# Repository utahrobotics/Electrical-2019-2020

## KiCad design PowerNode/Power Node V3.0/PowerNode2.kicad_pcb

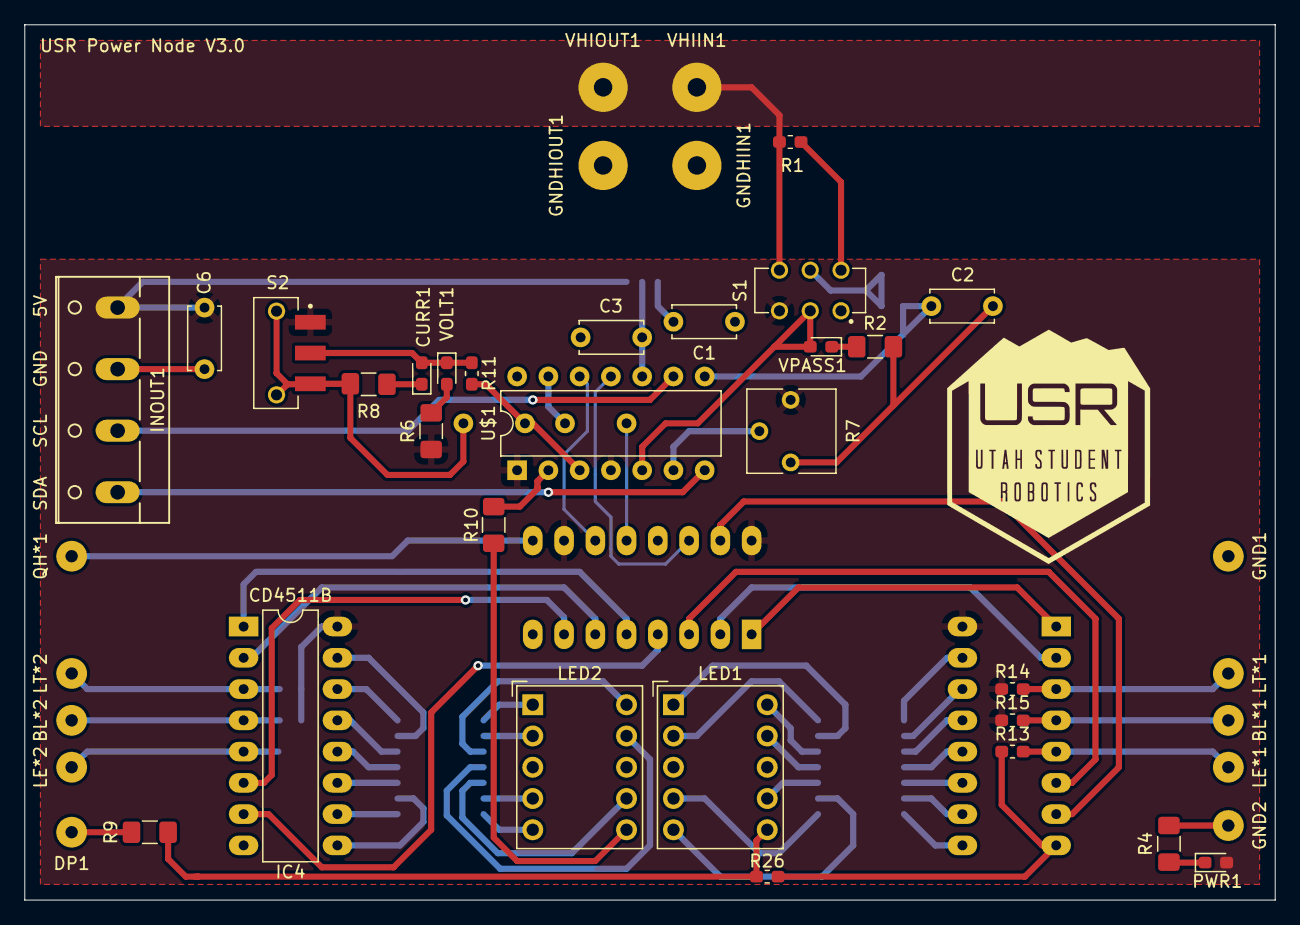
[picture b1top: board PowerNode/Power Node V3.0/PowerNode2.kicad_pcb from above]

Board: 2 copper layers, 101.6 x 71.1 mm, 55 parts (0 on the bottom side), 70 nets.

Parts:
BL*1, BL*2: 2,54_0,9; SolderWirePad_1x01_Drill1mm
C1: 1nF; C_Disc_D5.0mm_W2.5mm_P5.00mm
C2, C3, C4, C5, C6: 0.1uF; C_Disc_D5.0mm_W2.5mm_P5.00mm
CURR1: LED; LED_0603_1608Metric_Pad1.05x0.95mm_HandSolder
DP1: 2,54_0,9; SolderWirePad_1x01_Drill1mm
GND1, GND2: 2,15_1,0; SolderWirePad_1x01_Drill1mm
GNDHIIN1: WIREPAD4,16O1,6; SolderWirePad_1x01_Drill1.5mm
GNDHIOUT1: WIREPAD4,16O1,6; SolderWirePad_1x01_Drill1.5mm
IC1: ACS712xLCTR-30A; SOIC-8_3.9x4.9mm_P1.27mm
IC2: 74HC594N; DIP-16_W7.62mm_LongPads
IC3, IC4: CD4511B; DIP-16_W7.62mm_LongPads
INOUT1: W237-4
LE*1, LE*2: 2,54_0,9; SolderWirePad_1x01_Drill1mm
LED1, LED2: LTS-4301P; Sx39-1xxxxx
LT*1, LT*2: 2,54_0,9; SolderWirePad_1x01_Drill1mm
PWR1: LED; LED_0603_1608Metric_Pad1.05x0.95mm_HandSolder
QH*1: 2,54_0,9; SolderWirePad_1x01_Drill1mm
R1: 43k; R_0603_1608Metric_Pad1.05x0.95mm_HandSolder
R2, R4, R6, R8, R9, R10: 220; R_1206_3216Metric_Pad1.42x1.75mm_HandSolder
R3, R5, R11, R12, R13, R14, R15, R16, R17, R18, R26: 10k; R_0603_1608Metric_Pad1.05x0.95mm_HandSolder
R7: 100k; Potentiometer_Vishay_T73YP_Vertical
RN1, RN2: 220; SOIC127P762X240-14N
S1: JS202011CQN
S2: JS102011SAQN
U$1: ATtiny84-20PU; DIP-14_W7.62mm
VHIIN1: WIREPAD4,16O1,6; SolderWirePad_1x01_Drill1.5mm
VHIOUT1: WIREPAD4,16O1,6; SolderWirePad_1x01_Drill1.5mm
VOLT1: LED; LED_0603_1608Metric_Pad1.05x0.95mm_HandSolder
VPASS1: LED; LED_0603_1608Metric_Pad1.05x0.95mm_HandSolder

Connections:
/DP1: LED1.6, R9.2, R26.2
/DP2: LED2.6, R10.1
/GNDHIOUT: GNDHIOUT1.1, IC1.1, IC1.2
/IMEAS: C3.1, IC1.7, U$1.10
/SCL: INOUT1.2, U$1.9
/SDA: INOUT1.1, U$1.7
/SWITCH: CURR1.2, R11.2, S2.2, VOLT1.1
/VHI: R1.2, S1.6, VHIIN1.1, VHIOUT1.1
/VMEAS: R3.1, R5.1, S1.5
/VMEAS_1: C2.1, R5.2, U$1.8
/VPASS: S1.2, U$1.5, VPASS1.2
/VPOT: R7.2, U$1.6
/a1: LED1.10, RN1.5
/a2: LED2.10, RN2.10
/b1: LED1.9, RN1.4
/b2: LED2.9, RN2.11
/c1: LED1.7, RN1.3
/c2: LED2.7, RN2.12
/d1: LED1.5, RN1.2
/d2: LED2.5, RN2.14
/e1: LED1.4, RN1.1
/e2: LED2.4, RN2.13
/f1: LED1.2, RN1.7
/f2: LED2.2, RN2.9
/g1: LED1.1, RN1.6
/g2: LED2.1, RN2.8
/nBL1: BL*1.1, IC3.4, R15.2
/nBL2: BL*2.1, IC4.4, R18.2
/nLE1: IC3.5, LE*1.1, R13.2
/nLE2: IC4.5, LE*2.1, R16.2
/nLT1: IC3.3, LT*1.1, R14.2
/nLT2: IC4.3, LT*2.1, R17.2
/nQH: IC2.9, QH*1.1, R12.2
GND: C1.2, C2.2, C3.2, C5.2, C6.2, GND1.1, GND2.1, GNDHIIN1.1, IC1.3, IC1.4, IC1.5, IC2.8, IC2.13, IC3.8, IC4.8, INOUT1.3, LED1.3, LED1.8, LED2.3, LED2.8, R2.1, R3.2, R4.1, R7.3, R8.1, R12.1, R13.1, R16.1, R26.1, S1.1, S2.3, U$1.14
unnamed: C1.1, IC1.6
unnamed: C4.1, IC2.12
unnamed: C4.2, U$1.13
unnamed: C5.1, R11.1, U$1.3
unnamed: CURR1.1, R8.2
unnamed: DP1.1, R9.1
unnamed: IC2.1, IC3.1
unnamed: IC2.2, IC3.2
unnamed: IC2.3, IC3.6
unnamed: IC2.4, IC4.7
unnamed: IC2.5, IC4.1
unnamed: IC2.6, IC4.2
unnamed: IC2.7, IC4.6
unnamed: IC2.11, U$1.12
unnamed: IC2.14, U$1.11
unnamed: IC2.15, IC3.7
unnamed: IC3.9, RN1.14
unnamed: IC3.10, RN1.13
unnamed: IC3.11, RN1.12
unnamed: IC3.12, RN1.11
unnamed: IC3.13, RN1.10
unnamed: IC3.14, RN1.9
unnamed: IC3.15, RN1.8
unnamed: IC4.9, RN2.2
unnamed: IC4.10, RN2.1
unnamed: IC4.11, RN2.3
unnamed: IC4.12, RN2.4
unnamed: IC4.13, RN2.5
unnamed: IC4.14, RN2.7
unnamed: IC4.15, RN2.6
unnamed: PWR1.1, R4.2
unnamed: R1.1, S1.4
unnamed: R2.2, VPASS1.1
unnamed: R6.1, VOLT1.2
unnamed: R10.2, U$1.2
Vdd: C6.1, IC1.8, IC2.10, IC2.16, IC3.16, IC4.16, INOUT1.4, PWR1.2, R6.2, R7.1, R14.1, R15.1, R17.1, R18.1, S1.3, S2.1, U$1.1, U$1.4

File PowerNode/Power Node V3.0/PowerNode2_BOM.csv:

Item,Qty,Total Qty,Reference(s),Value,Footprint,Datasheet,Description,Status,Notes
1,1,6,C1,1nF,Capacitor_THT:C_Disc_D5.0mm_W2.5mm_P5.00mm,~,Ceramic capacitor,Buy from stockroom,
2,5,30,"C2, C3, C4, C5, C6",0.1uF,Capacitor_THT:C_Disc_D5.0mm_W2.5mm_P5.00mm,~,Ceramic capacitor,Buy from stockroom,
3,1,6,IC1,ACS712xLCTR-30A,Package_SO:SOIC-8_3.9x4.9mm_P1.27mm,http://www.allegromicro.com/~/media/Files/Datasheets/ACS712-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,Current sense IC,Already in the lab,
4,1,6,IC2,74HC594N,Package_DIP:DIP-16_W7.62mm_LongPads,http://www.ti.com/lit/ds/symlink/sn74hc594.pdf,Serial to parallel converter,Buy from stockroom,
5,2,12,"IC3, IC4",CD4511B,Package_DIP:DIP-16_W7.62mm_LongPads,https://www.ti.com/lit/ds/symlink/cd4511b.pdf,LED driver,Buy from stockroom,
6,1,6,INOUT1,W237-4,PowerNode2:W237-4,~,Screw terminal,Buy online,
7,2,12,"LED1, LED2",LTS-4301P,Display_7Segment:Sx39-1xxxxx,https://www.datasheets360.com/pdf/-3279684472568245476,7 segment display,Buy from stockroom,Make sure they are common cathode
8,2,12,"PWR1, VPASS1",LED,LED_SMD:LED_0603_1608Metric_Pad1.05x0.95mm_HandSolder,~,SMD LED,Buy online,Check If<=20mA and Vf<=3.3V. Prefer amber/orange/red for VPASS1
9,1,6,R1,43k,Resistor_SMD:R_0603_1608Metric_Pad1.05x0.95mm_HandSolder,~,SMD resistor,Buy online,Check 0603 package
10,6,36,"R2, R4, R6, R8-10",220,Resistor_SMD:R_1206_3216Metric_Pad1.42x1.75mm_HandSolder,~,SMD resistor,Buy online,Check 1206 package
11,11,66,"R3, R5, R11-18, R26",10k,Resistor_SMD:R_0603_1608Metric_Pad1.05x0.95mm_HandSolder,~,SMD resistor,Buy online,Check 0603 package
12,1,6,R7,100k,Potentiometer_THT:Potentiometer_Vishay_T73YP_Vertical,~,100k potentiometer,Buy from stockroom?,Make sure it fits
13,2,12,"RN1, RN2",220,PowerNode2:SOIC127P762X240-14N,https://www.mouser.com/datasheet/2/54/4800P-777115.pdf,SMD resistor network,Buy online,Cheaper than separate resistors and makes soldering easier
14,1,6,S1,SW_DPDT,PowerNode2:OS202011MS2Qx1,https://www.mouser.com/datasheet/2/60/os-1382783.pdf,DPDT switch,Buy online,
15,1,6,S2,SW_SPDT,PowerNode2:OS102011MS2Qx1,https://www.mouser.com/datasheet/2/60/os-1382783.pdf,SPDT switch,Buy online,
16,1,6,U$1,ATtiny84-20PU,Package_DIP:DIP-14_W7.62mm,http://ww1.microchip.com/downloads/en/DeviceDoc/doc8006.pdf,ATTiny84 microcontroller,Already in lab?,
17,1,6,VOLT1,HSMF-C173,PowerNode2:HSMFC173,https://docs.broadcom.com/docs/HSMF-C173-DS,SMD Bi-color LED,Buy online,Prefer colors different from VPASS1 and PWR1. Other similar package OK but tell me

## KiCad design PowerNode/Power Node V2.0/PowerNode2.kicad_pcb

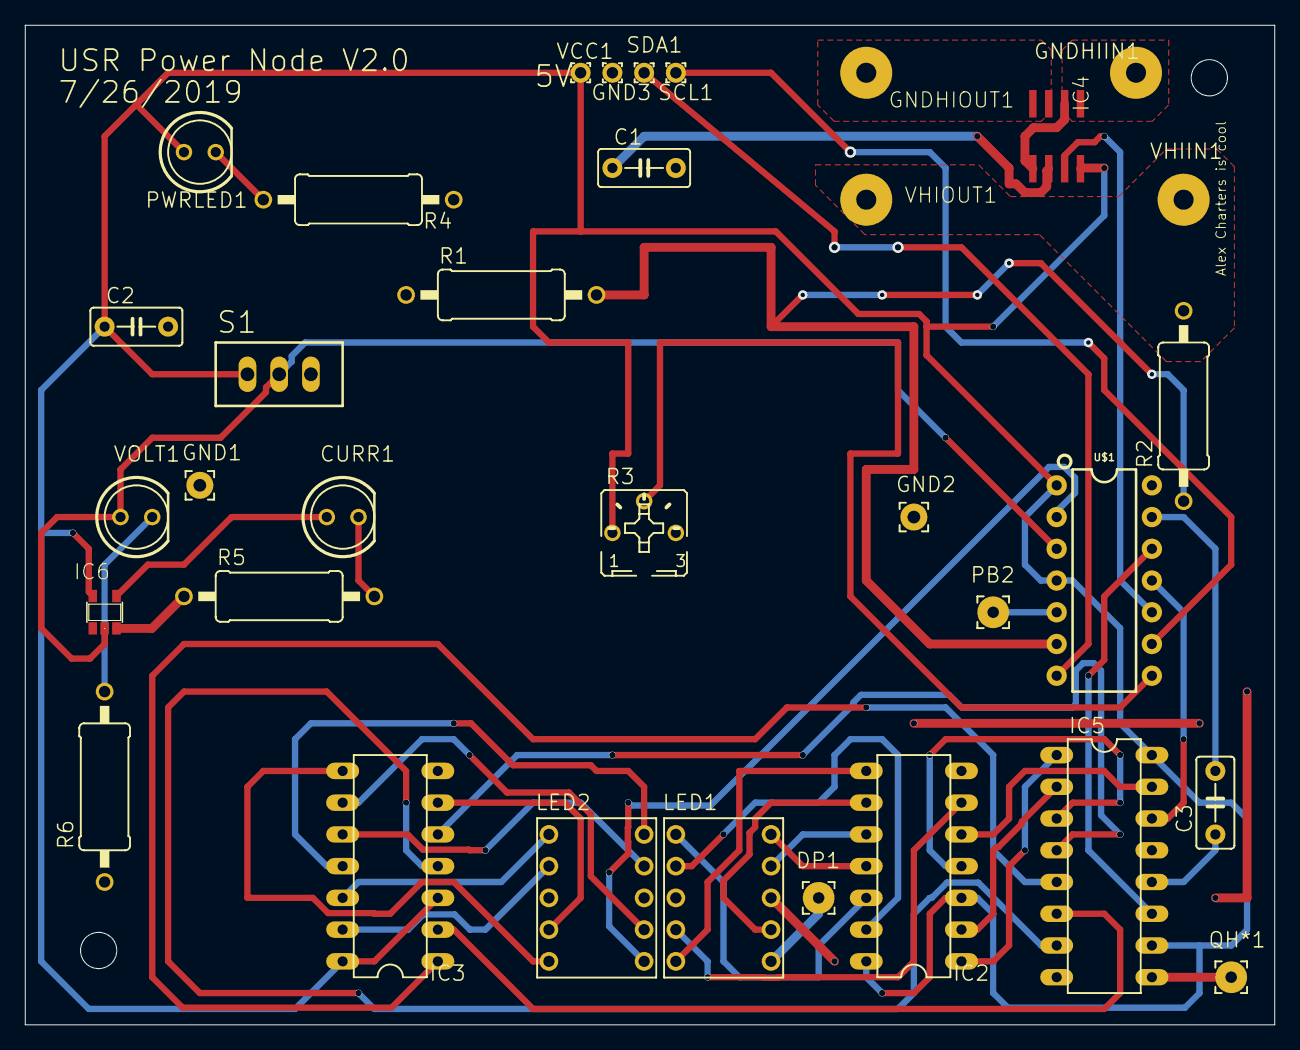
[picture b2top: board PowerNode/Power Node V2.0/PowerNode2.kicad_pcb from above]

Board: 2 copper layers, 100.0 x 80.0 mm, 36 parts (0 on the bottom side), 45 nets.

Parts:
@HOLE0, @HOLE1: (no value)
C1: 1nF; C5B3
C2, C3: 0.1uF; C5B3
CURR1: LED5MM
DP1: 2,54_0,9
GND1, GND2: 2,15_1,0
GND3: WIREPAD1,6_0,9; 1,6_0,9
GNDHIIN1: WIREPAD4,16O1,6; 4,16O1,6
GNDHIOUT1: WIREPAD4,16O1,6; 4,16O1,6
IC2, IC3: 7449N; DIL14
IC4: ACS712-LC; SOIC8
IC5: 74595N; DIL16
IC6: 741G04DBV; SOT23-5
LED1, LED2: S4301B
PB2: 2,54_0,9
PWRLED1: LED5MM
QH*1: 2,54_0,9
R1: 300k; 0411_15
R2: 1.2M; 0411_15
R3: TRIM_US-B25P; B25P
R4, R5, R6: 330; 0411_15
S1: TL32PO; TL3XPO
SCL1: WIREPAD1,6_0,9; 1,6_0,9
SDA1: WIREPAD1,6_0,9; 1,6_0,9
U$1: ATTINY84ATTINY84-20PU; DIP14
VCC1: WIREPAD1,6_0,9; 1,6_0,9
VHIIN1: WIREPAD4,16O1,6; 4,16O1,6
VHIOUT1: WIREPAD4,16O1,6; 4,16O1,6
VOLT1: LED5MM

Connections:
/VCC: C2.1, IC2.3, IC2.14, IC3.3, IC3.14, IC4.8, IC5.10, IC5.16, IC6.5, PWRLED1.A, R3.A, S1.1, U$1.1, U$1.4, VCC1.1
unnamed: C1.1, IC4.6
unnamed: C1.2, C2.2, GND1.1, GND2.1, GND3.1, GNDHIIN1.1, IC2.7, IC3.7, IC4.1, IC4.2, IC4.5, IC5.8, IC5.13, IC6.3, LED1.3, LED1.8, LED2.3, LED2.8, R1.1, R3.E, R4.1, R5.1, R6.1, S1.3, U$1.14
unnamed: C3.1, IC5.12
unnamed: C3.2, U$1.13
unnamed: CURR1.A, IC6.4
unnamed: CURR1.K, R5.2
unnamed: DP1.1, LED1.6
unnamed: GNDHIOUT1.1, IC4.3, IC4.4
unnamed: IC2.1, IC5.1
unnamed: IC2.2, IC5.2
unnamed: IC2.4, IC5.3
unnamed: IC2.5, IC5.15
unnamed: IC2.6, LED1.4
unnamed: IC2.8, LED1.5
unnamed: IC2.9, LED1.7
unnamed: IC2.10, LED1.9
unnamed: IC2.11, LED1.10
unnamed: IC2.12, LED1.1
unnamed: IC2.13, LED1.2
unnamed: IC3.1, IC5.5
unnamed: IC3.2, IC5.6
unnamed: IC3.4, IC5.7
unnamed: IC3.5, IC5.4
unnamed: IC3.6, LED2.4
unnamed: IC3.8, LED2.5
unnamed: IC3.9, LED2.7
unnamed: IC3.10, LED2.9
unnamed: IC3.11, LED2.10
unnamed: IC3.12, LED2.1
unnamed: IC3.13, LED2.2
unnamed: IC4.7, U$1.10
unnamed: IC5.9, QH*1.1
unnamed: IC5.11, U$1.12
unnamed: IC5.14, U$1.11
unnamed: IC6.2, S1.2, U$1.3, VOLT1.A
unnamed: LED2.6, U$1.2
unnamed: PB2.1, U$1.5
unnamed: PWRLED1.K, R4.2
unnamed: R1.2, R2.1, U$1.6
unnamed: R2.2, VHIIN1.1, VHIOUT1.1
unnamed: R3.S, U$1.8
unnamed: R6.2, VOLT1.K
unnamed: SCL1.1, U$1.9
unnamed: SDA1.1, U$1.7

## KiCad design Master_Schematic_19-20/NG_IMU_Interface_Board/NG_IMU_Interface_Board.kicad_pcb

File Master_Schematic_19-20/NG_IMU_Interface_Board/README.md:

# NG_IMU_Interface_Board
Hardware files for powering and interfacing with a Northrup Grumman IMU

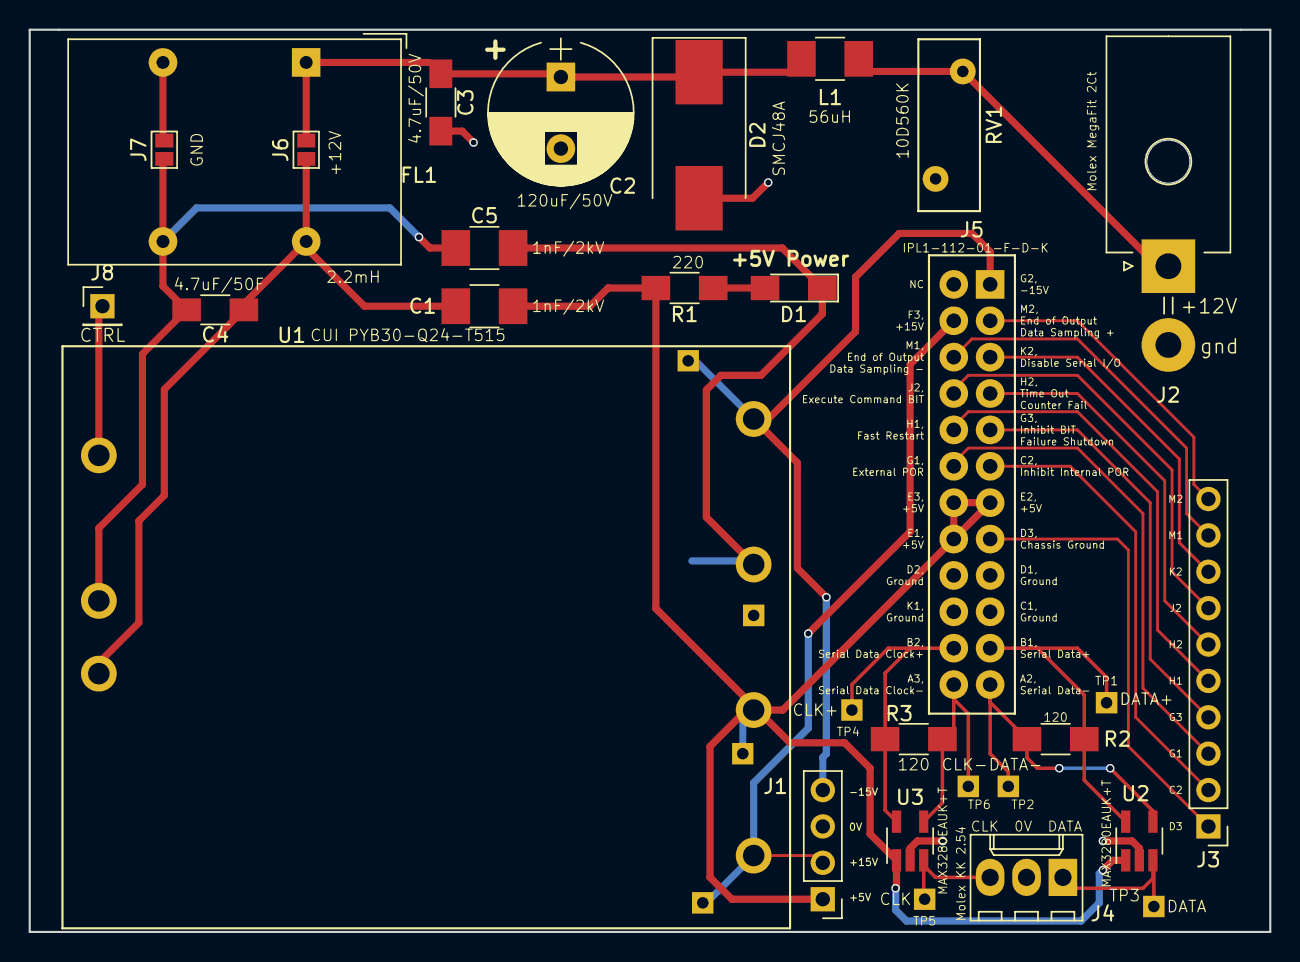
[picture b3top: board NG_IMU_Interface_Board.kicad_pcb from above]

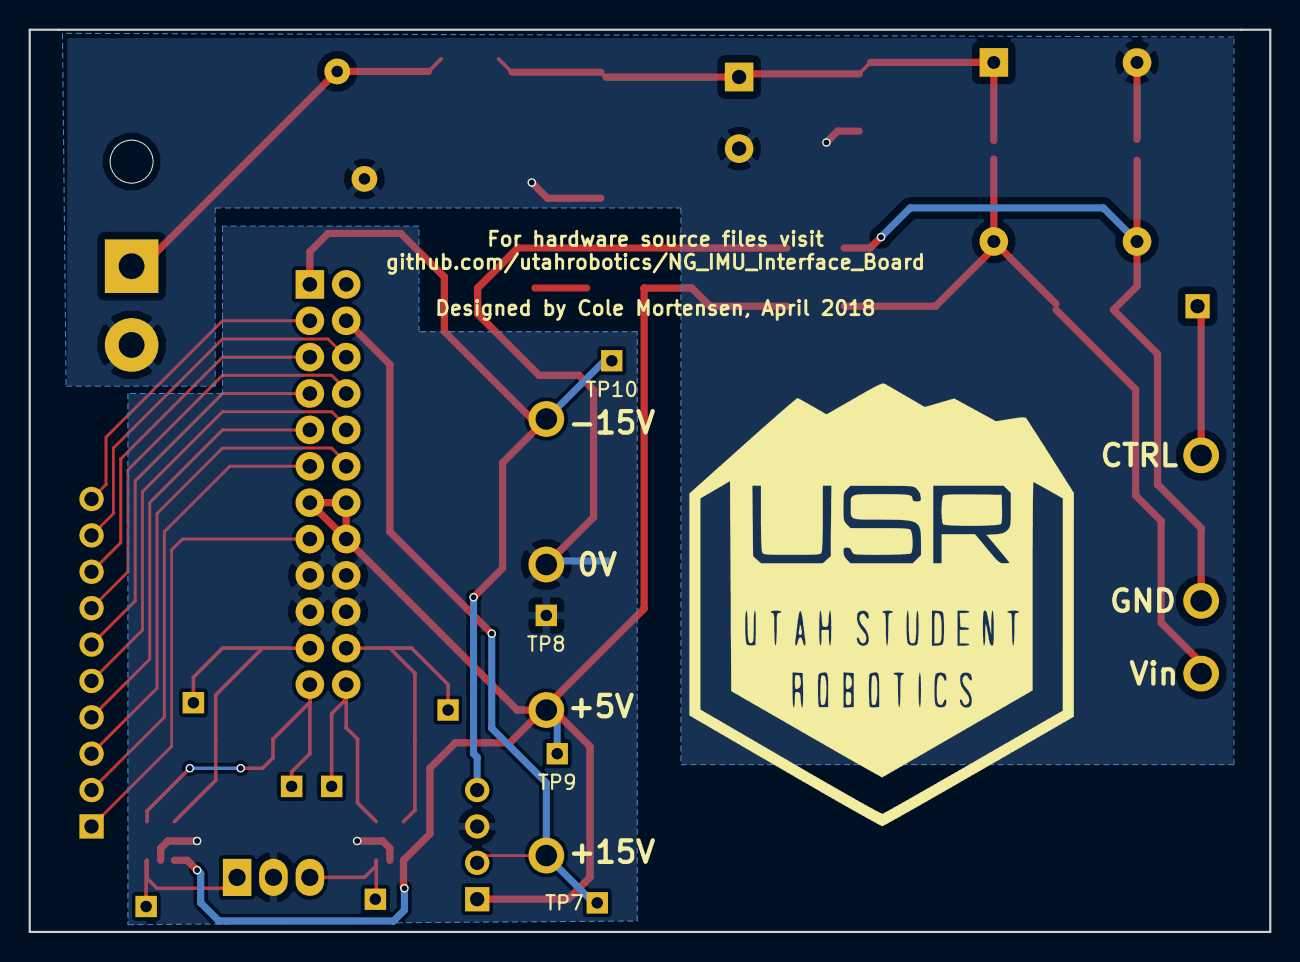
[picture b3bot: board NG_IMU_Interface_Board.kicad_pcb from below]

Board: 2 copper layers, 86.6 x 63.0 mm, 34 parts (4 on the bottom side), 27 nets.

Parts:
C1, C5: 1nF/2kV; C_1210_HandSoldering
C2: 120μF/50V; CP_Radial_D10.0mm_P5.00mm
C3, C4: 4.7μF/50V; C_1206_HandSoldering
D1: LED; LED_1206_HandSoldering
D2: SMCJ48A; D_SMC_Handsoldering
FL1: 2.2mH; Choke_Schaffner_RN214-04-15.5x23.0mm
J1: Conn_01x04; Pin_Header_Straight_1x04_Pitch2.54mm
J2: Conn_01x02; Molex_MegaFit_2x01x5.70mm_Angled
J3: Conn_01x10; Pin_Header_Straight_1x10_Pitch2.54mm
J4: Conn_01x03; Molex_KK-6410-03_03x2.54mm_Straight
J5: Conn_02x12_Top_Bottom; IPL1-112-01-F-D-K
J6, J7: GS2
J8: Conn_01x01; Pin_Header_Straight_1x01_Pitch2.54mm
L1: 56 uH; L_1210_HandSoldering
R1: 220; R_1206_HandSoldering
R2, R3: 120; R_1206_HandSoldering
RV1: 10D560K; RV_Disc_D12_W4.3_P7.5
TP1, TP2, TP3, TP4, TP5, TP6, TP7, TP8, TP9, TP10: TEST; Measurement_Point_Square-TH_Small
U1: PYB30-Q24-T515
U2, U3: MAX3280EAUK+T; SOT-23-5_HandSoldering

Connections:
/0V: C5.2, D1.1, J1.3, J4.2, J5.9, J5.10, J5.21, J5.22, TP8.1, U1.5, U2.2, U3.2
/+5V: C1.1, J1.1, J5.7, J5.19, J5.20, R1.2, TP9.1, U1.6, U2.1, U3.1
/+12V: J2.1, L1.1, RV1.2
/+15V: J1.2, J5.14, TP7.1, U1.7
/-15V: J1.4, J5.1, TP10.1, U1.4
/C2: J3.2, J5.6
/CLK+: J5.23, R3.2, TP4.1, U3.5
/CLK-: J5.24, R3.1, TP6.1, U3.4
/CLK_clean: J4.3, TP5.1, U3.3
/D3: J3.1, J5.8
/Data+: J5.11, R2.2, TP1.1, U2.5
/Data-: J5.12, R2.1, TP2.1, U2.4
/Data_clean: J4.1, TP3.1, U2.3
/G1: J3.3, J5.18
/G3: J3.4, J5.5
/H1: J3.5, J5.17
/H2: J3.6, J5.4
/J2: J3.7, J5.16
/K2: J3.8, J5.3
/M1: J3.9, J5.15
/M2: J3.10, J5.2
/gnd: C2.2, C3.2, D2.2, FL1.3, J2.2, J7.2, RV1.1
unnamed: C1.2, C4.1, FL1.2, J6.1, U1.1
unnamed: C2.1, C3.1, D2.1, FL1.1, J6.2, L1.2
unnamed: C4.2, C5.1, FL1.4, J7.1, U1.2
unnamed: D1.2, R1.1
unnamed: J8.1, U1.3

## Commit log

2019-10-01 added incomplete master schematic
2019-10-22 most up to date
2019-10-22 added snip
2019-10-22 pictures
2019-12-03 updated master schematic
2019-12-03 oops ignore last commit lmao XD I wanna die skeet skdefs
2020-01-03 added powernode slave code (not tested) and pinout diagram for attiny 84
2020-01-15 picture
2020-01-16 added electrical solidworks layout
2020-01-17 added eagle files
2020-01-17 Project cleanup
2020-01-17 Moved power node files to KiCAD
2020-01-17 Moved power node files to KiCAD
    Also removed old capture and added .gitignore
2020-01-17 Fixed a library renaming issue
2020-01-18 Added generated file for power node
2020-01-18 Added master schematic KiCAD files
2020-01-18 Added power node to master schematic
2020-01-18 Added motor controllers to master schematic
2020-01-18 Added agg-kicad library
2020-01-18 added more electrical components
2020-01-18 Added duplicate required motor controllers to master schematic
2020-01-18 Changed schematic paper size to A2 for more space
2020-01-18 Updated Roboclaw
2020-01-18 Added brushed motors to master schematic
2020-01-18 Added stepper motors to MS and small changes to Pololu3730.sch
2020-01-21 started wiring stuff
2020-01-21 added dependencies
2020-01-22 Added 3 more power nodes to master schematic
2020-01-22 Added IMU interface board files
2020-01-22 Annotated and updated schematic
2020-01-22 Added the real IMU interface board files
2020-01-22 Cleaned up the real IMU interface board schematic
2020-01-22 Added emergency stop button and cleaned up IMU interface board
2020-01-22 Added IMU interface board hierarchical pins and ODrive USB marker to MS
2020-01-26 Added Teensy 4 code
2020-02-04 added shift reg test
2020-02-05 Updated to schematic version 5 (sorted components)
2020-02-05 Added Jetson and updated drive motors (removed ODrive)
2020-02-07 .gitignore update
2020-02-07 Updated ground and IMU connections and added logic converter
2020-02-07 IMU Interface Board updates and improvements and general cleanup
2020-02-07 Updated IMU Interface Board libraries
2020-02-07 Cleanup .bck and fp-info-cache files
2020-02-08 working on powernode V3.0
2020-02-22 Added 2 new error signals to Teensy code
2020-02-22 Fixed IMU data scaling
2020-02-28 Removed old power node files and cleaned up master schematic
2020-02-28 PN3: schematic cleanup and moved logic to its own sheet
2020-02-28 PN3: added DPDT switch symbol and 3D switch models
2020-02-28 Power node 3.0 fixes, updates, and improvements
2020-02-28 Updated PN3 schematic to newer version and added/updated CL and PD resistors
2020-02-28 PN3: updated board and footprints
2020-02-28 PN3: updated PCB and added protective capacitors to VMEAS
2020-02-28 PN3: added spice models for switch, LEDs, LTS-4301P and ACS712
2020-02-28 PN3: removed R2 and replaced with a switched voltage divider
2020-02-28 PN3: changed resistors to use SMD footprints
2020-02-28 Removed BJTs and connected VMEAS directly
2020-02-28 PN3: added voltage follower to VMEAS and removed zener diode
2020-02-28 PN3: Improved ACS712 model, added simulation noise, and swapped IP+ and IP- order
2020-02-28 PN3 simulation fixes and updates (added models)
2020-02-28 PN3: datasheet update
2020-02-28 Remapped PN3 footprints
2020-02-28 PN3: Fixed potentiometer footprint mappings
2020-02-28 PN3: added ATTiny84 spice model and BJT models file
2020-02-28 PN3: added logic schematic (oops) and protective diode/capacitors for ATTiny inputs
2020-02-28 Added PN3 spice models for screw terminal and CD4511B plus generating script
2020-02-28 Remapped some components in power node v3.0
2020-02-28 Cleaned up PN3 10k resistors
2020-02-28 PN3: small simulation improvements
2020-02-28 PN3: removed 100uF capacitor and cleaned up some things
2020-02-28 PN3: added pull-down resistors for DP1 and QH*1
2020-02-28 PN3: corrected connection sorting
2020-02-28 PN3: updated footprints and 3D models
2020-02-28 PN3: Fixes for SPICE simulation
2020-02-28 Cleanup and connected logic ground to GND in PN3 schematic
2020-02-28 PN3: added labels, input voltage, and fixes to help with simulation
2020-02-28 PN3: board update/corrections
2020-02-28 Imported files to KiCAD
2020-03-03 PN3: small changes to DPDT symbol
2020-03-04 PN3: reannotated schematic and updated board
2020-03-04 PN3: connected 5V indicator to PB2 and other small changes
2020-03-04 PN3: improvements for simulation (added workbook)
2020-03-05 PN3: added better 3D switch models
2020-03-05 PN3: removed extra low-pass filter from IMEAS
2020-03-06 PN3: changed LEDs to SMD and VOLT1 to bi-color, other small changes
2020-03-07 PN3: changed to resistor networks from drivers and footprint/model cleanup
2020-03-07 PN3: added image and labels for prototyping
2020-03-09 IMU_Interface signal pin change
2020-03-09 Added serial printing for debug to IMU_Interface
2020-03-09 Updates from master
2020-03-09 Added new topic for raw data
2020-03-11 Sign error fixes and optimization using ldexp
2020-03-11 Fixes and optimizations to IMU_Interface code
2020-03-11 Cleaned up IMU_Interface code and added comments
2020-03-25 PN3: more routing changes
2020-03-25 PN3: Started routing and made appropriate adjustments
    One noteworthy adjustment was switching the VMEAS and VPOT pins
    on the ATTiny. The slave code was also updated.
2020-03-25 PN3: finished routing
2020-03-25 PN3: added models accidentally left out
2020-03-25 PN3: updated ATTiny code to use VPASS signal
2020-03-25 PN3: added logos and cleaned up connections
2020-03-25 PN3: updated 3D switch models
2020-03-25 PN3: created 3D models and small board changes
2020-03-25 PN3: added BOM and small board changes
2020-03-25 PN3: changed bi-color LED for separate LEDs and switches
2020-03-25 PN3: board fill and 3D model update
2020-03-26 PN3: updated switch board models
2020-03-27 PN3: made HI pads cover both sides
2020-03-27 PN3: board updates (placeholder)
2020-03-28 PN3: board reroute for higher current
2020-03-28 PN3: 3D model update
2020-03-29 Moved resistor networks out from under the seven segment displays to avoid soldering woes. Also, moved right-angle measure select switch to the side of the board for easy access.
2020-03-30 PN3: routing changes to reduce number of tracks and inductance
2021-10-23 Fixed a possible issue causing the clock interrupt to get detached much later than intended
2021-10-23 Simplified and fixed buffer logic
2021-10-23 Built updated code
2022-02-12 Updated for serial use
2022-02-12 Unbroke padding bit logic
2022-02-15 Still update timestamp when checksum fails
2022-02-16 Added more debug signals and small fix
2022-02-16 Added IMU initialization check and gravity offset
2022-02-16 Added init check for publishing and compiled
2022-02-17 Removed WFI to fix timing
2022-02-17 Small changes from master and for debug
2022-02-18 Added back bit reversal
2022-02-18 Better estimate for gravity in initialization
2022-02-18 Better gravity initialization and added normalized IMU message
2022-02-18 Added new publisher for normalized acceleration and fixed bit reversal
2022-02-18 Small changes and improvements
2022-02-19 Sync ROS timing and added spin timeout
2022-02-21 Added Twist and Transform publishers plus fixes and improvements
    - New publishers with improved gravity offset
    - IMU orientation in its frame of reference is considered zero
    - Rotation update now correctly uses IMU frame of reference
    - Other small fixes and readability improvements
2022-02-22 Updated for ROS debug with no IMU connected
2022-02-22 Added generated test data
2022-02-23 Timing fixes and added debug messages
2022-02-23 Debug improvements and small fix to init acceleration to gravity
2022-02-24 Simplified for USB debug
2022-02-24 Added separate error topic and improved time reporting
2022-02-25 Improved debug messages and publishing
2022-02-25 Added output signals for better debugging
2022-02-25 Added debug topic, improved publishing, and small fixes
2022-02-26 Improved error checking, correct DT when data is bad, and fixed gravity initialization
2022-02-26 Code cleanup
2022-03-05 Updated ROS library
2022-03-05 Updated to build correctly with rosserial setup
2022-03-05 Updates from master and small fixes/improvements
2022-03-05 Fixed issues in sending and receiving bits and added more debug printing
2022-03-05 No longer using reverse trapezoid rule
2022-03-05 Added more debug printing, no more reverse trapezoid rule, and fixes
